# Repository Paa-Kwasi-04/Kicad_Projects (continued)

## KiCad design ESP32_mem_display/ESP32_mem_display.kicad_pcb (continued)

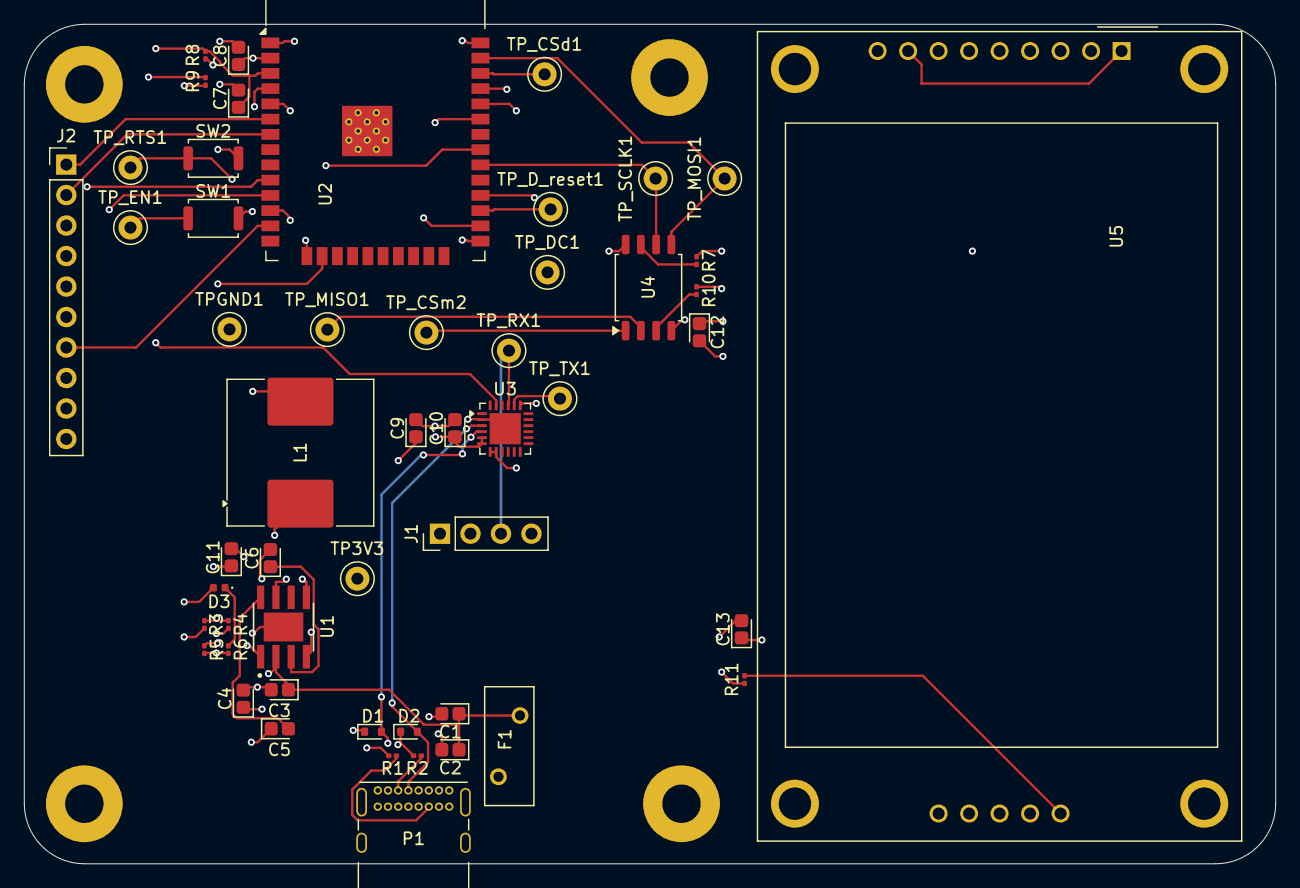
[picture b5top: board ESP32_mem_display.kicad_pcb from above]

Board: 4 copper layers, 104.2 x 69.9 mm, 56 parts (0 on the bottom side), 38 nets.

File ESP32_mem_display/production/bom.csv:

Designator,Footprint,Quantity,Value,LCSC Part #
"C1, C13, C3",CP_EIA-1608-10_AVX-L,3,10uF,
"C10, C12, C8, C9",CP_EIA-1608-10_AVX-L,4,0.1µF,
"C11, C4, C5",CP_EIA-1608-10_AVX-L,3,22uF,
C2,CP_EIA-1608-10_AVX-L,1,0.1uF,
C6,CP_EIA-1608-10_AVX-L,1,10nF,
C7,CP_EIA-1608-10_AVX-L,1,100nF,
"D1, D2",D_SOD-523,2,ESD5Zxx,
D3,0402,1,LED,
F1,Fuse_BelFuse_0ZRE0025FF_L9.6mm_W3.8mm,1,Fuse,
J1,PinHeader_1x04_P2.54mm_Vertical,1,UART header,
J2,PinHeader_1x10_P2.54mm_Vertical,1,GPIO,
L1,L_Coilcraft_MSS1246H-XXX,1,3uH,
P1,USB_C_Receptacle_GCT_USB4085,1,USB_C_Plug_USB2.0,
"R1, R2",0201,2,5.1KΩ,
"R10, R11, R5, R7, R8, R9",0201,6,10KΩ,
R3,0201,1,31KΩ,
R4,0201,1,100KΩ,
R6,0201,1,1KΩ,
"SW1, SW2",SW_Push_SPST_NO_Alps_SKRK,2,SW_Push,
"TP3V3, TPGND1, TP_CSD1, TP_CSM2, TP_DC1, TP_D_RESET1, TP_EN1, TP_MISO1, TP_MOSI1, TP_RTS1, TP_RX1, TP_SCLK1, TP_TX1",TestPoint_Keystone_5000-5004_Miniature,13,TestPoint,
U1,MP1584EN_Buck_convertor,1,MP1584EN-LF-Z,
U2,ESP32-WROOM-32,1,ESP32-WROOM-32,
U3,QFN-24-1EP_4x4mm_P0.5mm_EP2.6x2.6mm,1,CP2102N-Axx-xQFN24,
U4,SOIC-8_5.3x5.3mm_P1.27mm,1,W25Q128JVS,
U5,CR2013-MI2120,1,CR2013-MI2120,

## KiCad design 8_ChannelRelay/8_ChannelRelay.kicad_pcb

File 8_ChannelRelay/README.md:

# 8 Channel Relay

## Description
This is an 8-channel relay board design for controlling multiple high-power devices or circuits. Each relay channel can be independently controlled to switch AC or DC loads. This board is commonly used in home automation, industrial control systems, and other applications requiring multiple switched outputs.

## Features
- 8 independent relay channels
- Suitable for controlling multiple loads
- Compatible with microcontroller control (Arduino, ESP32, etc.)
- Can switch both AC and DC loads

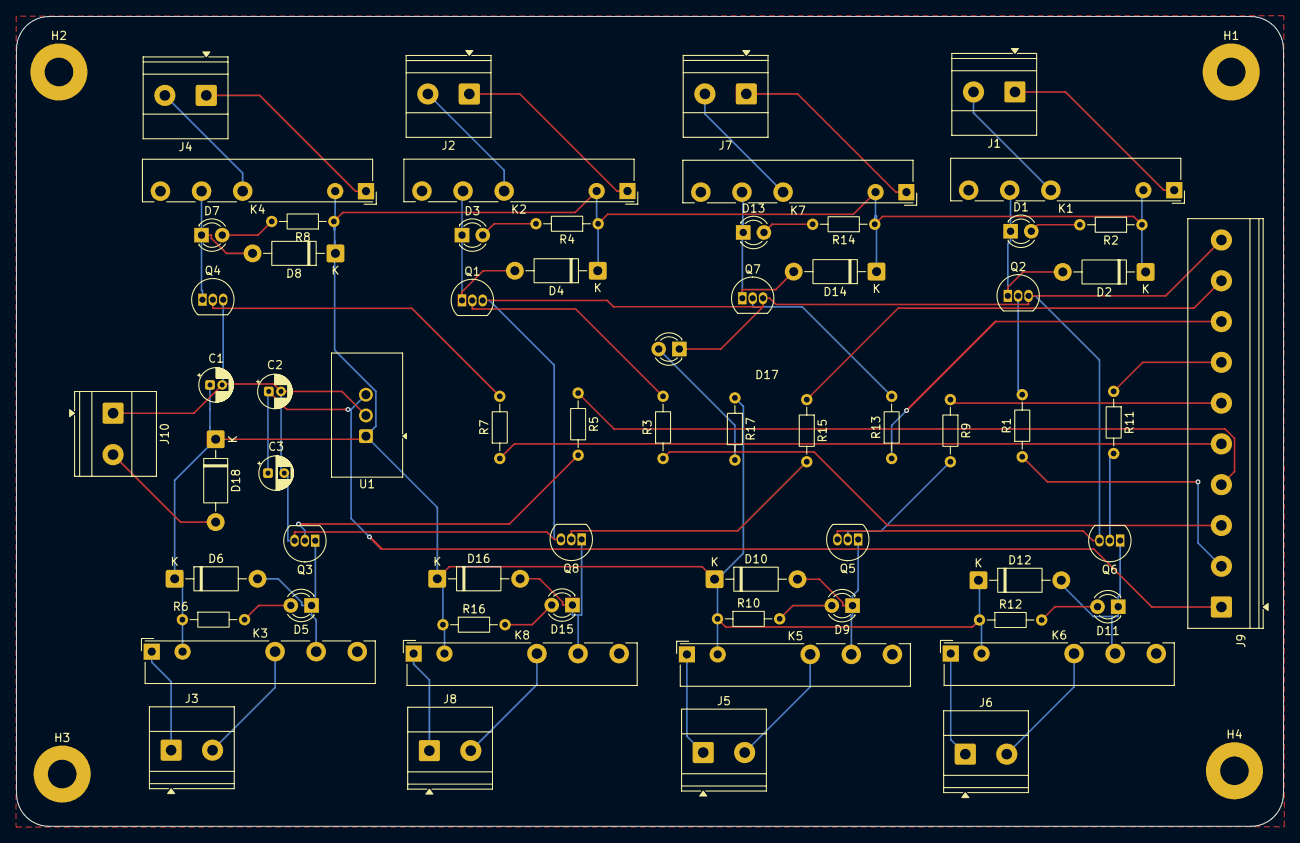
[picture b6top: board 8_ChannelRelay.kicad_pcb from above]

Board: 2 copper layers, 155.3 x 99.3 mm, 69 parts (0 on the bottom side), 53 nets.

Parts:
C1, C2: 1uF; CP_Radial_D4.0mm_P1.50mm
C3: 100uF; CP_Radial_D4.0mm_P2.00mm
D1, D3, D5, D7, D9, D11, D13, D15, D17: LED; LED_D3.0mm
D2, D4, D6, D8, D10, D12, D14, D16, D18: 1N4007; D_DO-41_SOD81_P10.16mm_Horizontal
H1, H2, H3, H4: MountingHole; MountingHole_3.5mm_Pad
J1, J2, J3, J4, J5, J6, J7, J8: Screw_Terminal_01x03; TerminalBlock_Phoenix_MKDS-1,5-2-5.08_1x02_P5.08mm_Horizont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
J9: Screw_Terminal_01x10; TerminalBlock_Phoenix_PT-1,5-10-5.0-H_1x10_P5.00mm_Horizont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
J10: Screw_Terminal_01x02; TerminalBlock_Phoenix_MKDS-1,5-2-5.08_1x02_P5.08mm_Horizont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
K1, K2, K3, K4, K5, K6, K7, K8: Fujitsu_FTR-LYCA005x; Relay_SPDT_Fujitsu_FTR-LYCA005x_FormC_Vertical
Q1, Q2, Q3, Q4, Q5, Q6, Q7, Q8: BC547; TO-92_Inline
R1, R3, R5, R7, R9, R11, R13, R15, R17: 1k; R_Axial_DIN0204_L3.6mm_D1.6mm_P7.62mm_Horizontal
R2, R4, R6, R8, R10, R12, R14, R16: 330; R_Axial_DIN0204_L3.6mm_D1.6mm_P7.62mm_Horizontal
U1: TSR2-24120; Converter_DCDC_TRACO_TSR2-xxxx_THT

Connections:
+12V: C1.1, D2.1 (K), D4.1 (K), D6.1 (K), D8.1 (K), D10.1 (K), D12.1 (K), D14.1 (K), D16.1 (K), D18.1 (K), K1.A2, K2.A2, K3.A2, K4.A2, K5.A2, K6.A2, K7.A2, K8.A2, R2.1, R4.1, R6.1, R8.1, R10.1, R12.1, R14.1, R16.1, R17.1, U1.1 (Vin)
GND: C1.2, C2.2, C3.2, D17.1 (K), J9.10, J10.1, Q1.3 (E), Q2.3 (E), Q3.3 (E), Q4.3 (E), Q5.3 (E), Q6.3 (E), Q7.3 (E), Q8.3 (E), U1.2 (GND)
unnamed: D1.2 (A), R2.2
unnamed: D1.1 (K), D2.2 (A), K1.11, Q2.1 (C)
unnamed: D3.2 (A), R4.2
unnamed: D3.1 (K), D4.2 (A), K2.11, Q1.1 (C)
unnamed: D5.2 (A), R6.2
unnamed: D5.1 (K), D6.2 (A), K3.11, Q3.1 (C)
unnamed: D7.2 (A), R8.2
unnamed: D7.1 (K), D8.2 (A), K4.11, Q4.1 (C)
unnamed: D9.2 (A), R10.2
unnamed: D9.1 (K), D10.2 (A), K5.11, Q5.1 (C)
unnamed: D11.2 (A), R12.2
unnamed: D11.1 (K), D12.2 (A), K6.11, Q6.1 (C)
unnamed: D13.2 (A), R14.2
unnamed: D13.1 (K), D14.2 (A), K7.11, Q7.1 (C)
unnamed: D15.2 (A), R16.2
unnamed: D15.1 (K), D16.2 (A), K8.11, Q8.1 (C)
unnamed: D17.2 (A), R17.2
unnamed: D18.2 (A), J10.2
unnamed: J1.1, K1.A1
unnamed: J1.2, K1.12
unnamed: J2.1, K2.A1
unnamed: J2.2, K2.12
unnamed: J3.1, K3.A1
unnamed: J3.2, K3.12
unnamed: J4.1, K4.A1
unnamed: J4.2, K4.12
unnamed: J5.1, K5.A1
unnamed: J5.2, K5.12
unnamed: J6.1, K6.A1
unnamed: J6.2, K6.12
unnamed: J7.1, K7.A1
unnamed: J7.2, K7.12
unnamed: J8.1, K8.A1
unnamed: J8.2, K8.12
unnamed: Q1.2 (B), R3.2
unnamed: Q2.2 (B), R1.2
unnamed: Q3.2 (B), R5.2
unnamed: Q4.2 (B), R7.2
unnamed: Q5.2 (B), R9.2
unnamed: Q6.2 (B), R11.2
unnamed: Q7.2 (B), R13.2
unnamed: Q8.2 (B), R15.2
Relay1: J9.2, R1.1
Relay2: J9.3, R3.1
Relay3: J9.4, R5.1
Relay4: J9.5, R7.1
Relay5: J9.6, R9.1
Relay6: J9.7, R11.1
Relay7: J9.8, R13.1
Relay8: J9.9, R15.1
VCC: C2.1, C3.1, J9.1, U1.3 (Vout)

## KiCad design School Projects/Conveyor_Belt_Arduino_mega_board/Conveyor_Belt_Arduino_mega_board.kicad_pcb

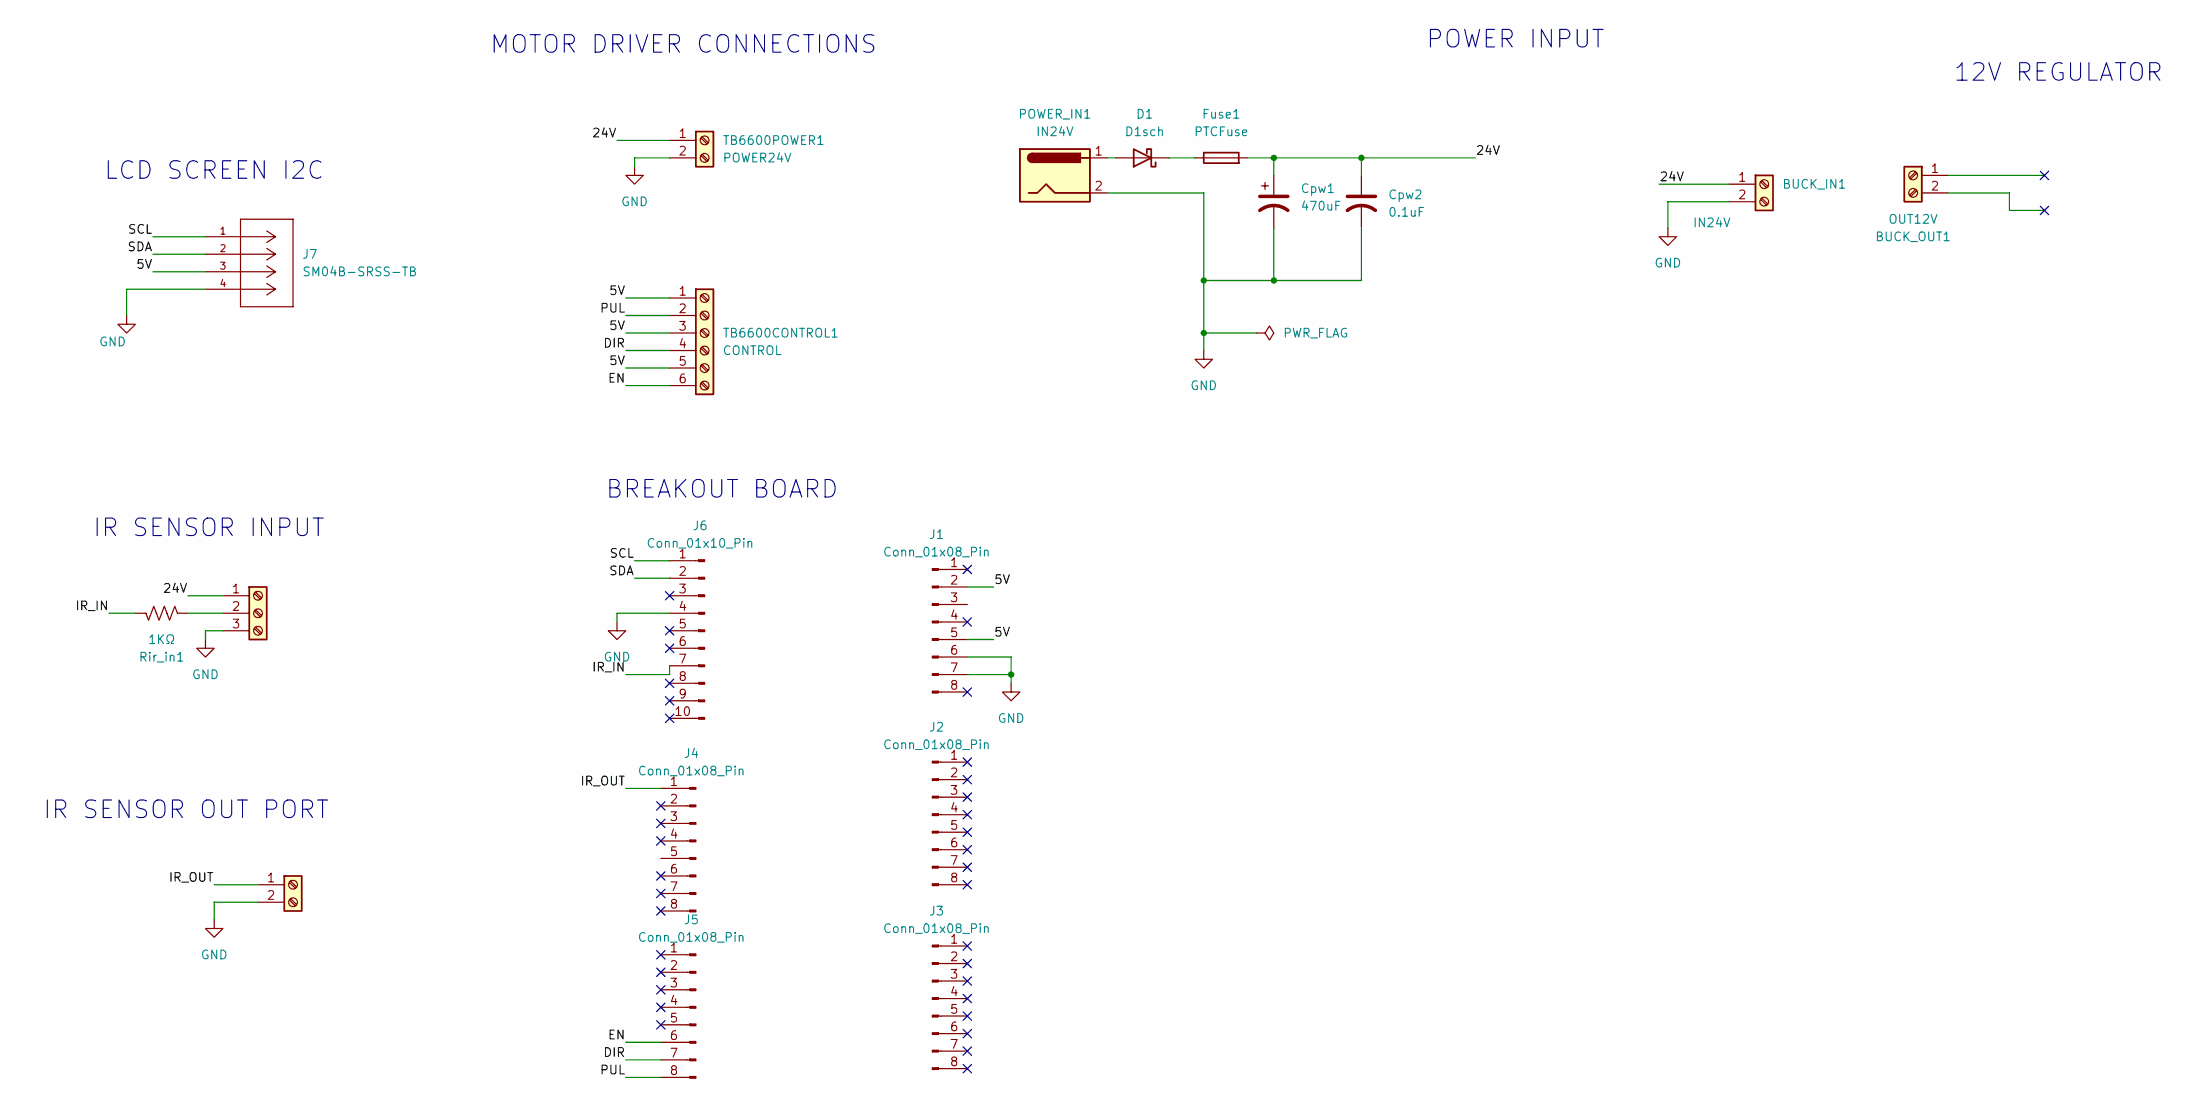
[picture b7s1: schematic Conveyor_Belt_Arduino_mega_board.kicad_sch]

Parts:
BUCK_IN1: IN24V; TerminalBlock_Phoenix_MKDS-1,5-2_1x02_P5.00mm_Horizontal
BUCK_OUT1: OUT12V; TerminalBlock_Phoenix_MKDS-1,5-2_1x02_P5.00mm_Horizontal
Cpw1: 470uF; CP_Axial_L10.0mm_D4.5mm_P15.00mm_Horizontal
Cpw2: 0.1uF; CP_Axial_L10.0mm_D4.5mm_P15.00mm_Horizontal
D1: D1sch; D_A-405_P12.70mm_Horizontal
Fuse1: PTCFuse; Fuse_Bourns_MF-RG400
J1, J2, J3, J4, J5: Conn_01x08_Pin; PinHeader_1x08_P2.54mm_Vertical
J6: Conn_01x10_Pin; PinHeader_1x10_P2.54mm_Vertical
J7: SM04B-SRSS-TB; CONN_SM04B-SRSS-TB_JST; MANUFACTURER_PART_NUMBER SM04B-SRSS-TB
POWER_IN1: IN24V; TerminalBlock_Phoenix_MKDS-1,5-2_1x02_P5.00mm_Horizontal
Rir_in1: 1KΩ; R_Axial_DIN0309_L9.0mm_D3.2mm_P12.70mm_Horizontal
SENSOR_IN1: TerminalBlock_Phoenix_MKDS-1,5-3-5.08_1x03_P5.08mm_Horizont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
SENSOR_OUT1: TerminalBlock_Phoenix_MKDS-1,5-2_1x02_P5.00mm_Horizontal
TB6600CONTROL1: CONTROL; TerminalBlock_Phoenix_MKDS-1,5-6_1x06_P5.00mm_Horizontal
TB6600POWER1: POWER24V; TerminalBlock_Phoenix_MKDS-1,5-2_1x02_P5.00mm_Horizontal

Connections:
/5V: J1.2, J1.5, J7.3, TB6600CONTROL1.1, TB6600CONTROL1.3, TB6600CONTROL1.5
/24V: BUCK_IN1.1, Cpw1.1, Cpw2.1, Fuse1.2, SENSOR_IN1.1, TB6600POWER1.1
/DIR: J5.7, TB6600CONTROL1.4
/EN: J5.6, TB6600CONTROL1.6
/IR_IN: J6.7, Rir_in1.1
/IR_OUT: J4.1, SENSOR_OUT1.1
/PUL: J5.8, TB6600CONTROL1.2
/SCL: J6.1, J7.1
/SDA: J6.2, J7.2
GND: BUCK_IN1.2, Cpw1.2, Cpw2.2, J1.6, J1.7, J6.4, J7.4, POWER_IN1.2, SENSOR_IN1.3, SENSOR_OUT1.2, TB6600POWER1.2; also elsewhere on the board
unnamed: D1.2 (A), POWER_IN1.1
unnamed: D1.1 (K), Fuse1.1
unnamed: Rir_in1.2, SENSOR_IN1.2

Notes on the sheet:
12V REGULATOR
BREAKOUT BOARD
LCD SCREEN I2C
POWER INPUT
IR SENSOR INPUT
MOTOR DRIVER CONNECTIONS
IR SENSOR OUT PORT

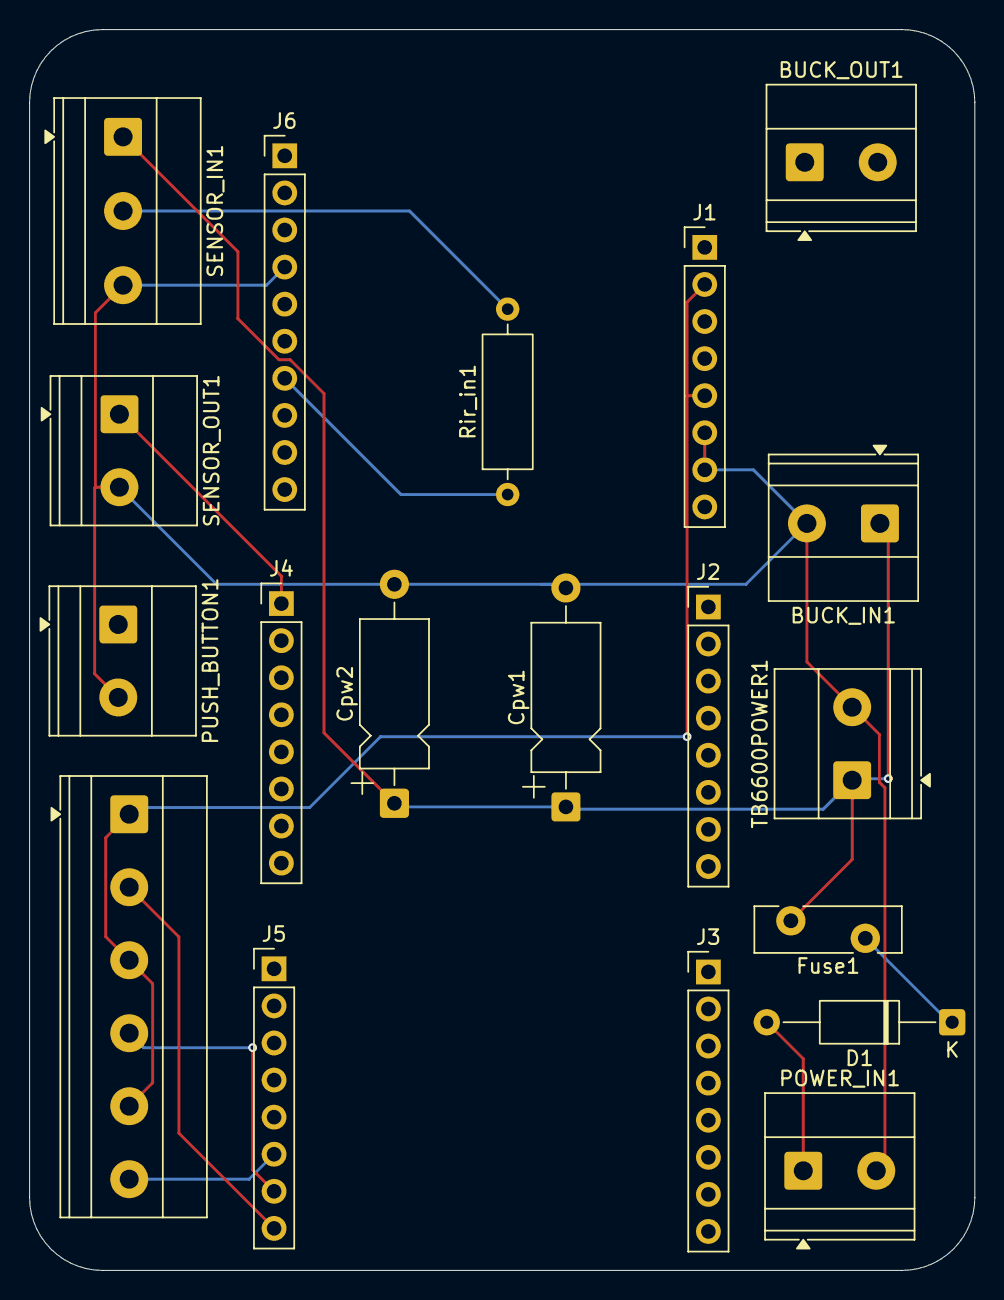
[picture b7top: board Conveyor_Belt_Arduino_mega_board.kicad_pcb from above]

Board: 2 copper layers, 64.8 x 85.0 mm, 19 parts (0 on the bottom side), 11 nets.

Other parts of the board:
PUSH_BUTTON1: TerminalBlock_Phoenix_MKDS-1,5-2_1x02_P5.00mm_Horizontal

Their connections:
GND: PUSH_BUTTON1.2; also elsewhere on the board

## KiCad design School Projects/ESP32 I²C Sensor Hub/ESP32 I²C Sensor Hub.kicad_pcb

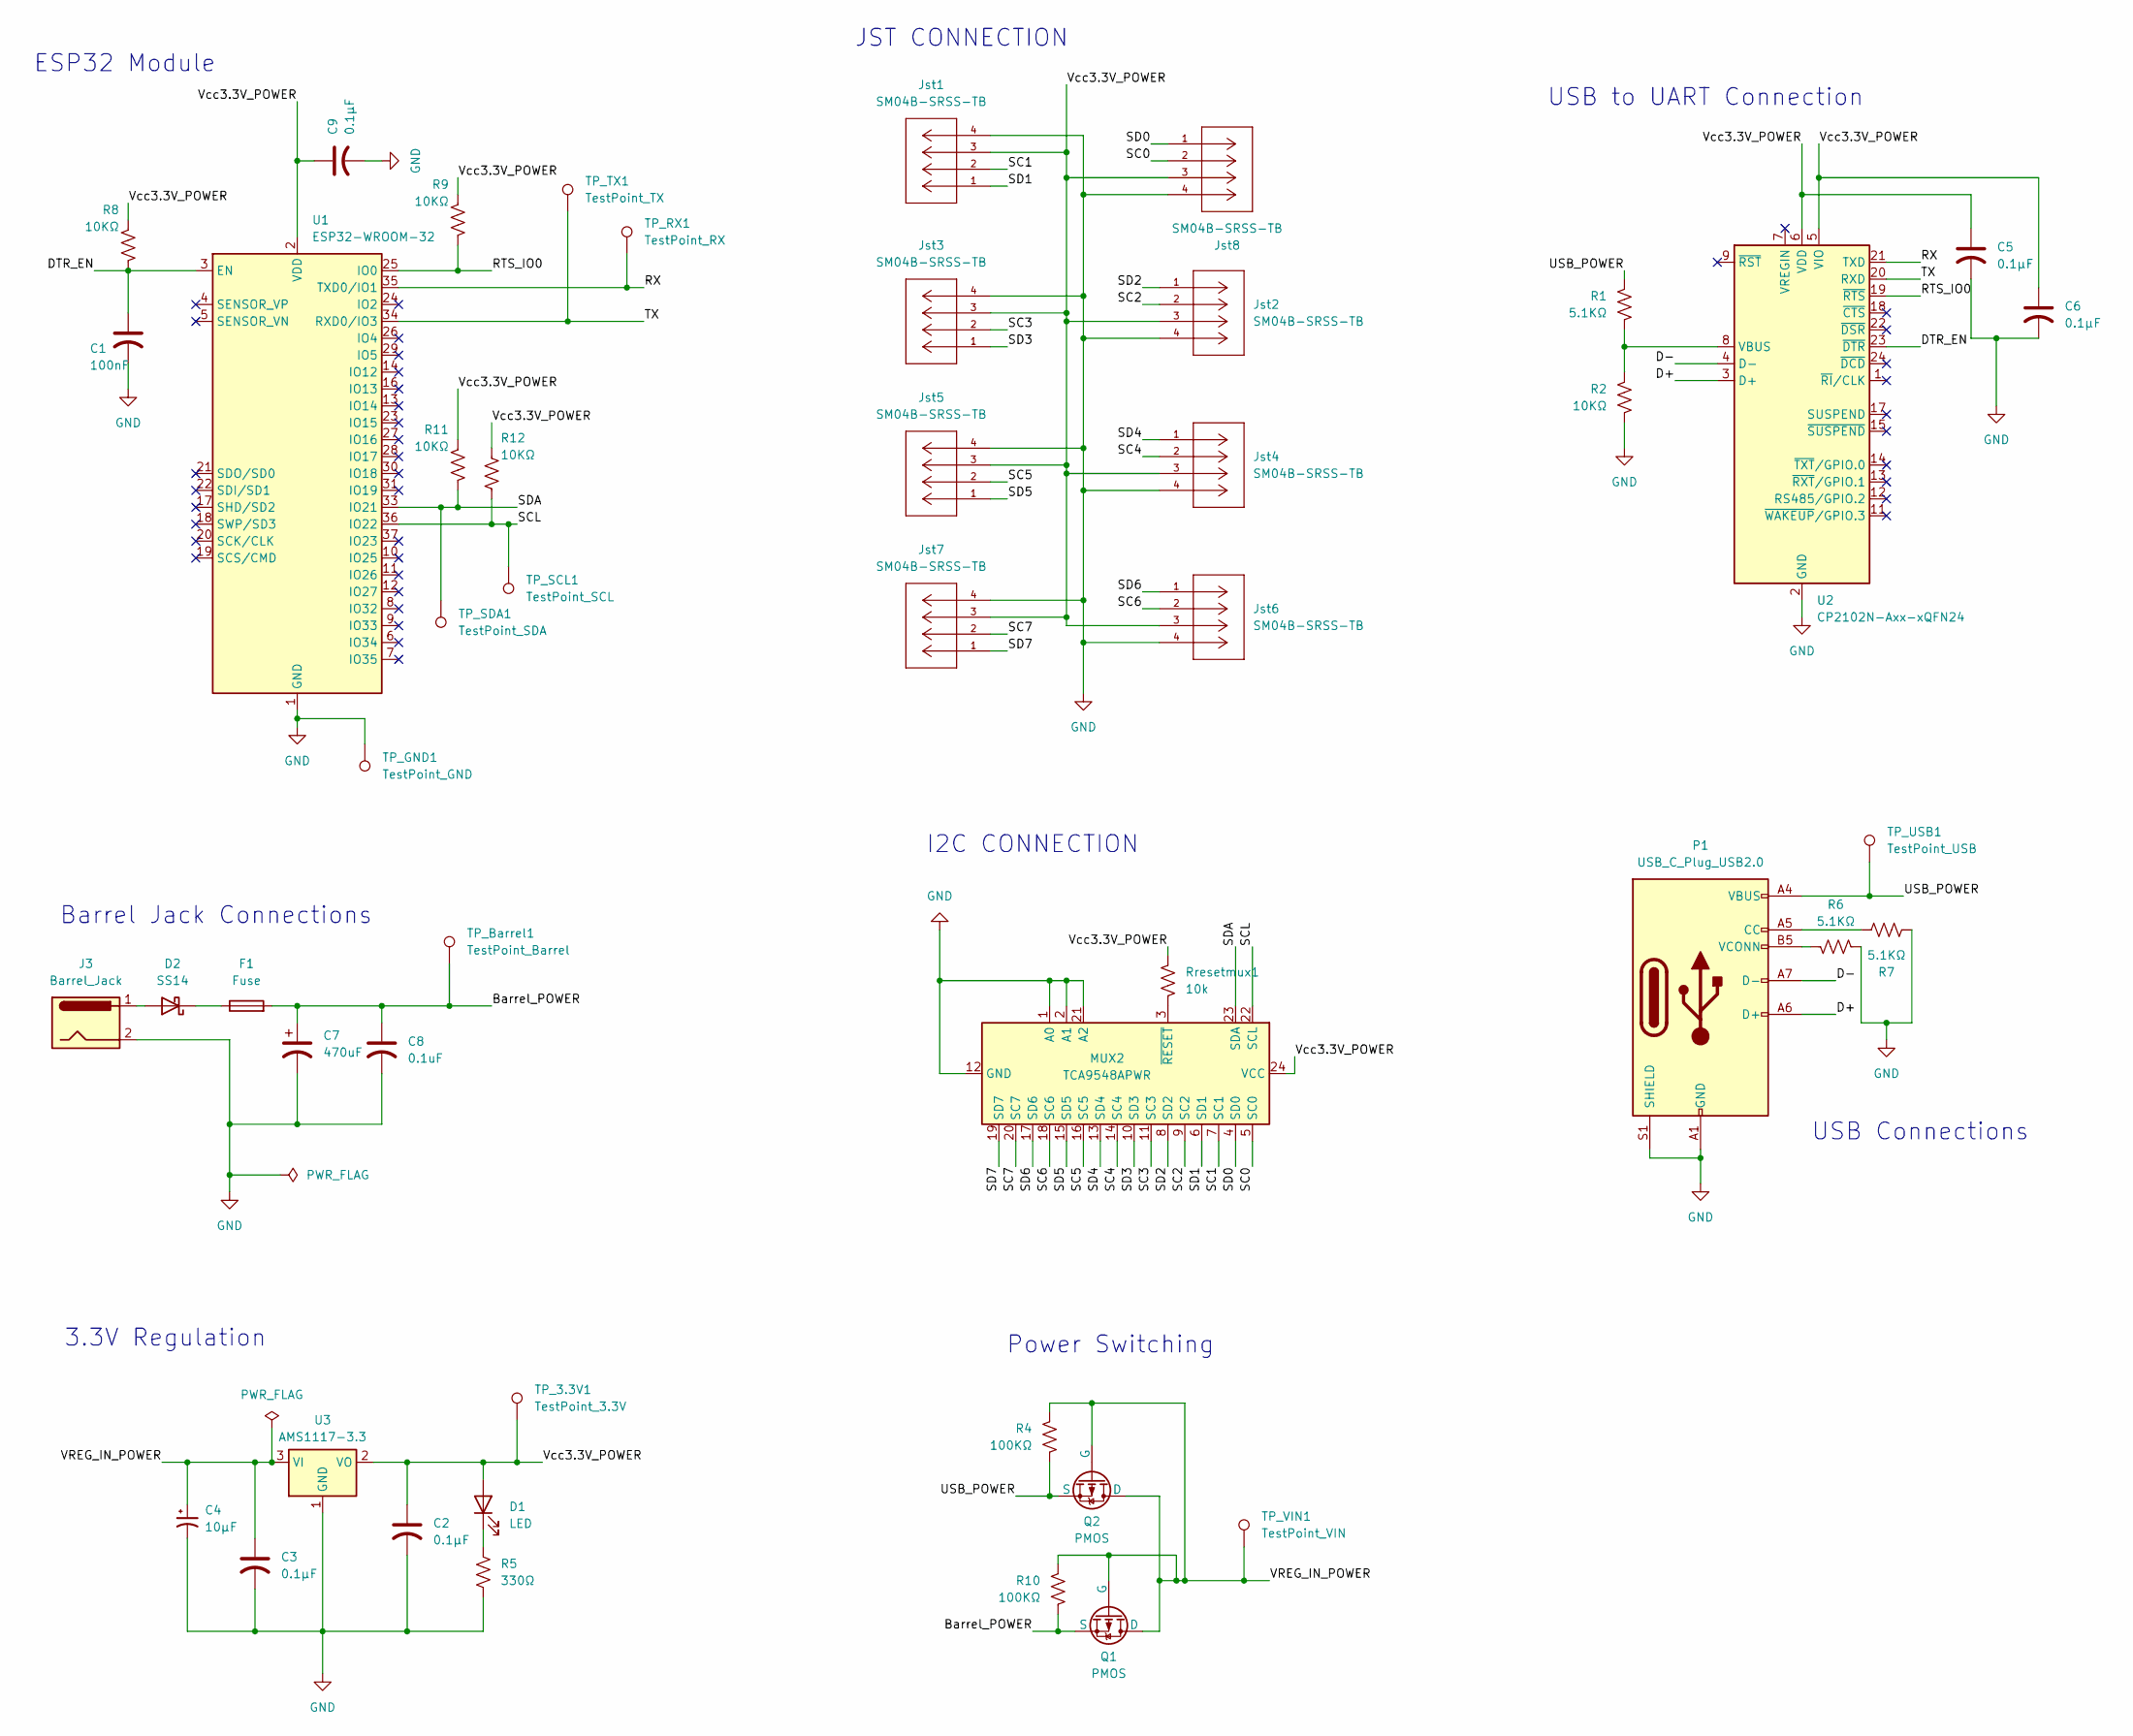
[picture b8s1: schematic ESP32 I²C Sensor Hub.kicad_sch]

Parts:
C1: 100nF; CP_EIA-1608-10_AVX-L
C2, C3, C5, C6, C9: 0.1µF; CP_EIA-1608-10_AVX-L
C4: 10µF; CP_EIA-1608-10_AVX-L
C7: 470uF; CP_EIA-1608-10_AVX-L
C8: 0.1uF; CP_EIA-1608-10_AVX-L
D1: LED; LED_0201_0603Metric
D2: SS14; D_0603_1608Metric_Pad1.05x0.95mm_HandSolder
F1: Fuse; Fuse_0603_1608Metric
J3: Barrel_Jack; BarrelJack_GCT_DCJ200-10-A_Horizontal
Jst1, Jst2, Jst3, Jst4, Jst5, Jst6, Jst7, Jst8: SM04B-SRSS-TB; JST_GH_BM04B-GHS-TBT_1x04-1MP_P1.25mm_Vertical; MANUFACTURER_PART_NUMBER SM04B-SRSS-TB
MUX2: TCA9548APWR; TSSOP-24_4.4x7.8mm_P0.65mm
P1: USB_C_Plug_USB2.0; USB_C_Receptacle_GCT_USB4085
Q1, Q2: PMOS; SuperSOT-3
R1, R6, R7: 5.1KΩ; R_0201_0603Metric
R2, R8, R9, R11, R12: 10KΩ; R_0201_0603Metric
R4, R10: 100KΩ; R_0201_0603Metric
R5: 330Ω; R_0201_0603Metric
Rresetmux1: 10k; R_0805_2012Metric_Pad1.20x1.40mm_HandSolder
TP_3.3V1: TestPoint_3.3V; TestPoint_Bridge_Pitch2.0mm_Drill0.7mm
TP_Barrel1: TestPoint_Barrel; TestPoint_Bridge_Pitch2.0mm_Drill0.7mm
TP_GND1: TestPoint_GND; TestPoint_Bridge_Pitch2.0mm_Drill0.7mm
TP_RX1: TestPoint_RX; TestPoint_Bridge_Pitch2.0mm_Drill0.7mm
TP_SCL1: TestPoint_SCL; TestPoint_Bridge_Pitch2.0mm_Drill0.7mm
TP_SDA1: TestPoint_SDA; TestPoint_Bridge_Pitch2.0mm_Drill0.7mm
TP_TX1: TestPoint_TX; TestPoint_Bridge_Pitch2.0mm_Drill0.7mm
TP_USB1: TestPoint_USB; TestPoint_Bridge_Pitch2.0mm_Drill0.7mm
TP_VIN1: TestPoint_VIN; TestPoint_Bridge_Pitch2.0mm_Drill0.7mm
U1: ESP32-WROOM-32
U2: CP2102N-Axx-xQFN24; QFN-24-1EP_4x4mm_P0.5mm_EP2.6x2.6mm
U3: AMS1117-3.3; SOT-223-3_TabPin2

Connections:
/Barrel_POWER: C7.1, C8.1, F1.2, Q1.3 (S), R10.2, TP_Barrel1.1
/D+: P1.A6 (D+), U2.3 (D+)
/D-: P1.A7 (D-), U2.4 (D-)
/DTR_EN: C1.1, R8.2, U1.3 (EN), U2.23 (~DTR)
/RTS_IO0: R9.2, U1.25 (IO0), U2.19 (~RTS)
/RX: TP_RX1.1, U1.35 (TXD0/IO1), U2.21 (TXD)
/SC0: Jst8.2, MUX2.5 (SC0)
/SC1: Jst1.2, MUX2.7 (SC1)
/SC2: Jst2.2, MUX2.9 (SC2)
/SC3: Jst3.2, MUX2.11 (SC3)
/SC4: Jst4.2, MUX2.14 (SC4)
/SC5: Jst5.2, MUX2.16 (SC5)
/SC6: Jst6.2, MUX2.18 (SC6)
/SC7: Jst7.2, MUX2.20 (SC7)
/SCL: MUX2.22 (SCL), R12.2, TP_SCL1.1, U1.36 (IO22)
/SD0: Jst8.1, MUX2.4 (SD0)
/SD1: Jst1.1, MUX2.6 (SD1)
/SD2: Jst2.1, MUX2.8 (SD2)
/SD3: Jst3.1, MUX2.10 (SD3)
/SD4: Jst4.1, MUX2.13 (SD4)
/SD5: Jst5.1, MUX2.15 (SD5)
/SD6: Jst6.1, MUX2.17 (SD6)
/SD7: Jst7.1, MUX2.19 (SD7)
/SDA: MUX2.23 (SDA), R11.2, TP_SDA1.1, U1.33 (IO21)
/TX: TP_TX1.1, U1.34 (RXD0/IO3), U2.20 (RXD)
/USB_POWER: P1.A4 (VBUS), P1.A9 (VBUS), P1.B4 (VBUS), P1.B9 (VBUS), Q2.3 (S), R1.2, R4.2, TP_USB1.1
/VREG_IN_POWER: C3.1, C4.1, Q1.1 (D), Q1.2 (G), Q2.1 (D), Q2.2 (G), R4.1, R10.1, TP_VIN1.1, U3.3 (VI)
/Vcc3.3V_POWER: C2.1, C5.1, C6.1, C9.1, D1.2 (A), Jst1.3, Jst2.3, Jst3.3, Jst4.3, Jst5.3, Jst6.3, Jst7.3, Jst8.3, MUX2.24 (VCC), R8.1, R9.1, R11.1, R12.1, Rresetmux1.1, TP_3.3V1.1, U1.2 (VDD), U2.5 (VIO), U2.6 (VDD), U3.2 (VO)
GND: C1.2, C2.2, C3.2, C4.2, C5.2, C6.2, C7.2, C8.2, C9.2, J3.2, Jst1.4, Jst2.4, Jst3.4, Jst4.4, Jst5.4, Jst6.4, Jst7.4, Jst8.4, MUX2.1 (A0), MUX2.2 (A1), MUX2.12 (GND), MUX2.21 (A2), P1.A1 (GND), P1.A12 (GND), P1.B1 (GND), P1.B12 (GND), P1.S1 (SHIELD), R2.1, R5.2, R6.2, R7.2, TP_GND1.1, U1.1 (GND), U1.15 (GND), U1.38 (GND), U1.39 (GND), U2.2 (GND), U2.25 (GND), U3.1 (GND)
unnamed: D1.1 (K), R5.1
unnamed: D2.2 (A), J3.1
unnamed: D2.1 (K), F1.1
unnamed: MUX2.3 (~RESET), Rresetmux1.2
unnamed: P1.A5 (CC), R7.1
unnamed: P1.B5 (VCONN), R6.1
unnamed: R1.1, R2.2, U2.8 (VBUS)

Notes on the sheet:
I2C CONNECTION
Power Switching
ESP32 Module
USB Connections
JST CONNECTION
Barrel Jack Connections
3.3V Regulation
USB to UART Connection

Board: 2 copper layers, 49 parts (0 on the bottom side), 36 nets, no tracks yet.

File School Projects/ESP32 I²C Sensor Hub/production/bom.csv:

Designator,Footprint,Quantity,Value,LCSC Part #
C1,CP_EIA-1608-10_AVX-L,1,100nF,
"C2, C3, C5, C6, C9",CP_EIA-1608-10_AVX-L,5,0.1µF,
C4,CP_EIA-1608-10_AVX-L,1,10µF,
C7,CP_EIA-1608-10_AVX-L,1,470uF,
C8,CP_EIA-1608-10_AVX-L,1,0.1uF,
D1,0201,1,LED,
D2,0603,1,SS14,
F1,0603,1,Fuse,
J3,BarrelJack_GCT_DCJ200-10-A_Horizontal,1,Barrel_Jack,
"JST1, JST2, JST3, JST4, JST5, JST6, JST7, JST8",JST_GH_BM04B-GHS-TBT_1x04-1MP_P1.25mm_Vertical,8,SM04B-SRSS-TB,
MUX2,TSSOP-24_4.4x7.8mm_P0.65mm,1,TCA9548APWR,
P1,USB_C_Receptacle_GCT_USB4085,1,USB_C_Plug_USB2.0,
"Q1, Q2",SuperSOT-3,2,PMOS,
"R1, R6, R7",0201,3,5.1KΩ,
"R10, R4",0201,2,100KΩ,
"R11, R12, R2, R8, R9",0201,5,10KΩ,
R5,0201,1,330Ω,
RMUX1,0201,1,10k,
TP_3.3V1,TestPoint_Plated_Hole_D2.0mm,1,TestPoint_3.3V,
TP_BARREL1,TestPoint_Plated_Hole_D2.0mm,1,TestPoint_Barrel,
TP_GND1,TestPoint_Plated_Hole_D2.0mm,1,TestPoint_GND,
TP_RX1,TestPoint_Plated_Hole_D2.0mm,1,TestPoint_RX,
TP_SCL1,TestPoint_Plated_Hole_D2.0mm,1,TestPoint_SCL,
TP_SDA1,TestPoint_Plated_Hole_D2.0mm,1,TestPoint_SDA,
TP_TX1,TestPoint_Plated_Hole_D2.0mm,1,TestPoint_TX,
TP_USB1,TestPoint_Plated_Hole_D2.0mm,1,TestPoint_USB,
TP_VIN1,TestPoint_Plated_Hole_D2.0mm,1,TestPoint_VIN,
U1,ESP32-WROOM-32,1,ESP32-WROOM-32,
U2,QFN-24-1EP_4x4mm_P0.5mm_EP2.6x2.6mm,1,CP2102N-Axx-xQFN24,
U3,SOT-223-3_TabPin2,1,AMS1117-3.3,

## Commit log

2025-07-11 feat:Added some kicad projects
2025-07-21 feat:new projects
2025-07-21 ods:Mosquito project
2025-07-21 mods:Mosquito repellant
2025-08-13 ods:8ch relay
2025-08-13 mods
2025-09-03 ods to the file structure
2025-09-03 placed all projects in new dir
2025-09-08 finished schematic of chaser board
2025-09-16 added prod of chaser board,updates to car battery detector and started simple power supply project
2025-09-18 added prod of simple power supply project
2025-09-25 Added pcb design of multiple sensor display module as well as fab of power supply board
2025-09-29 mods to display sensor module pcb routing
2025-10-11 Added Coneyor belt main board project
2025-10-11 deleted power_supply voard kicad_sch.lck file
2025-10-11 moved this lib to another dir
2025-10-20 Finished conveyor belt pcb ready for prob
2025-10-20 Added Sensor and display module
2025-10-20 First commit of esp32 clone with only schematic
2025-10-22 yet to assign footprints in next commit
2025-10-29 Final parts of esp32 board
2025-11-03 Fully functioning esp32 clone board with pcb prod files
2025-11-03 Deleted a lib from the sensor and display module pcb
2025-11-03 Added png of pcbs of earlier projects
2025-11-03 Changed dir stuct of Esp32 pcb
2025-11-06 Changed dir structure of fais projects and deleted some dir
2025-11-06 Added new Esp32 sensor hub project working schematic
2025-11-10 Added final fab files for esp32 sensor port
2025-11-24 StereAudio Processor with PCB and prod files
2025-11-25 Restructed Esp32 sensor hub dir
2025-11-25 Other version of the conveyor main boarh but with an arduino mega board instead of just the chip
2025-12-23 Removed some unnecessary parts like reset button and emergency stop based on final production board
2025-12-23 Changed dir stuct and added pics of some boards
2025-12-23 Some more changes to dir stuct
2025-12-23 Initial plan
2025-12-23 Add README.md files to all KiCad project folders with PNG images
2025-12-23 Add detailed descriptions to all KiCad project READMEs and create main repository README
2025-12-24 Final prod kicad files for first 4 layer Esp32 dev board clone
2025-12-24 Add README for ESP32S3 4-layer board and update main README
2025-12-24 Clarify ESP32 module specification in README files
2025-12-25 Fixed some errors from routing traces
2025-12-25 Esp32 layer board with spi memory and display has prod files also
2025-12-25 Add ESP32_mem_display project documentation and update main README
2025-12-27 Finished 4 layer Buck convertor with prod files
2025-12-27 Add README for Buck Converter 4-Layer project and update main README
2025-12-27 Fix spelling consistency: use 'Convertor' to match repository convention
2025-12-29 Made slight changes to the routing by removing traces in the ground plane and fixing also some drc errors
2025-12-29 Added new Motor driver project using a DRV8871 motor driver IC
2025-12-29 Add Motor Driver 4-layer project to README and create project README
2026-01-02 Added Stepper motor driver 4 layer pcb with it prob files
2026-01-02 Re-routed some traces and removed unsure vias
2026-01-04 Added Battery Power Management System with prob files
2026-01-04 Add README files for Battery Power Management and Stepper Motor Driver boards, update main README
